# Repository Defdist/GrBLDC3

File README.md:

# GrBLDC3
Uno Shield for grblDD: closed loop spindle VFD + 4 stepper drivers

Main Controller PCB for GG3.  Hardware version 3B
This is the 1st PCB shipped in GG3.

PCB designed in KiCAD.

Changes (from the previous prototype PCB):

-3-pin header order changed from VGS to VSG (e.g. from +-X to +X-).  This creates an incompatibility issue with GG2 units, which will require a pin swap.

-Removed Door Switch (which also restored previous gap for zip tie).

-Vref changed to 1.78 volts (added 1k series with pulldown).

-Added two additional stepper power modes, to reduce power consumption at idle, and to (briefly) increase power if X axis is binding, or if BLDC controller is bogged down in a corner.

-Stepper X1 is now disabled unless A0_STEP_X1_EN is pulled high... this pin is shared with 64M1 reset, which means that when the X1 stepper (only) is disabled, the spindle will not spin.

-Replaced 2x1 screw terminal probe connector with 5x1 SIP.  This is now the only wire harness that goes to LED PCB.  24V and 5V are current limited on this PCB, so that metal chips contacting LED PCB don't affect GrBLDC.

-Added Zener protection diode to 5V rail, in the hope that if 24V finds its way onto that rail, the zener will short it out... this will of course burn out the zener, but hopefully by then the PTC on the Uno will have opened.

-Fixed incorrect pinout on A4910 (pins 39 & 40 swapped).

-BLDC Hall connector changed from 1x5 to 2x3, to make assembling easier.  6th pin is now connected to spindle wipers.

-Removed 2x3 64M1 programming header; connected SPI to Arduino pins instead.  328p can now program this part in-situ (via temporarily loading SPI bitbang firmware onto 328p).

-Emergency stop now pulls BLDC and stepper drivers into reset.

-Emergency stop interface to 328p fixed, such that computer can now pulse reset line during firmware updates.  When estop enabled, 328p continuously held in reset.

-Z stepper connector changed to 2x2, so that it fits through gantry bushings.

-24V/GND/GND 45 degree connector now fits (moved fan connector and capacitors).

New Parts:  
LED PCB:  
102-5777-ND  
Get longer right angle SIPs for LED PCB  
LED - 732-5660-1-ND

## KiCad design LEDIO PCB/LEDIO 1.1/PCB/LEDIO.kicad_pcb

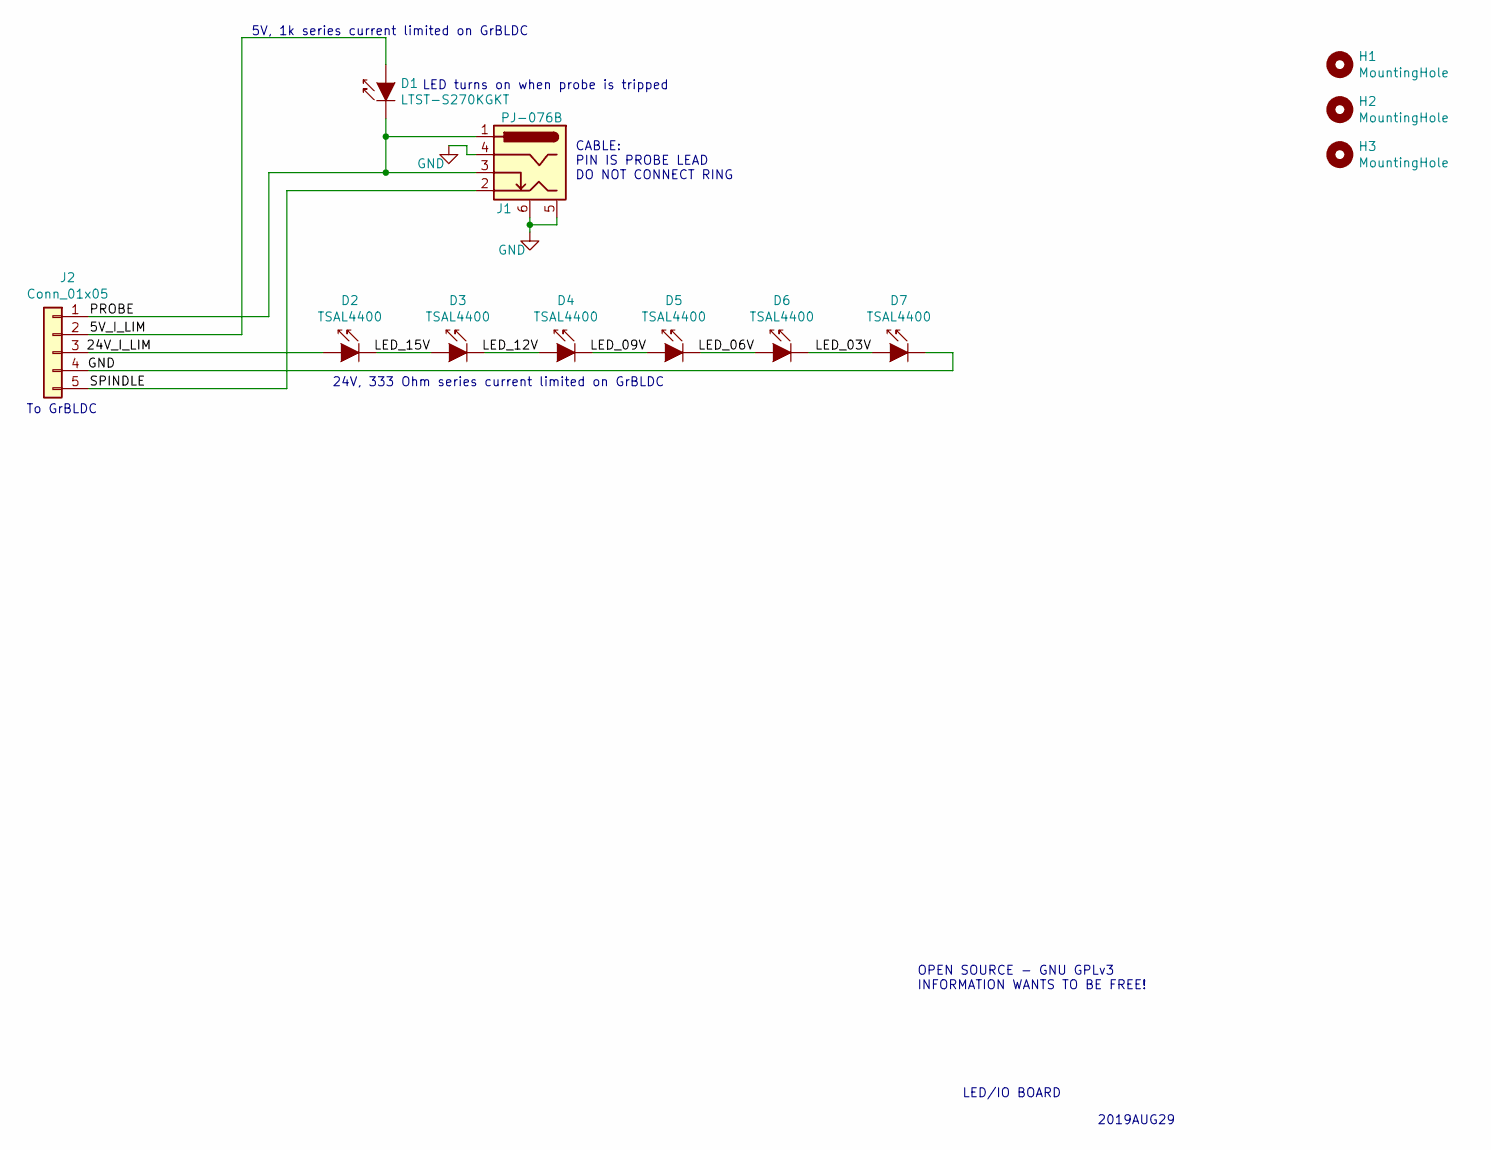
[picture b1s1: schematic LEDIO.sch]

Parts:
D1: LTST-S270KGKT; D_0603_1608Metric
D2, D3, D4, D5, D6, D7: TSAL4400; D_1206_3216Metric
H1, H2, H3: MountingHole; MountingHole_3.2mm_M3
J1: PJ-076B; CUI_PJ-076
J2: Conn_01x05; PinHeader_1x05_P2.54mm_Horizontal

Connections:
/5V_I_LIM: D1.2 (A), J2.2
/24V_I_LIM: D2.2 (A), J2.3
/LED_03V: D6.1 (K), D7.2 (A)
/LED_06V: D5.1 (K), D6.2 (A)
/LED_09V: D4.1 (K), D5.2 (A)
/LED_12V: D3.1 (K), D4.2 (A)
/LED_15V: D2.1 (K), D3.2 (A)
/PROBE: D1.1 (K), J1.1, J1.3, J2.1
/SPINDLE: J1.2, J2.5
GND: D7.1 (K), J1.4, J1.5 (ShieldA), J1.6 (ShieldB), J2.4

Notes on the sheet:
CABLE: PIN IS PROBE LEAD DO NOT CONNECT RING
2019AUG29
LED/IO BOARD
OPEN SOURCE - GNU GPLv3 INFORMATION WANTS TO BE FREE!
5V, 1k series current limited on GrBLDC
To GrBLDC
LED turns on when probe is tripped
24V, 333 Ohm series current limited on GrBLDC

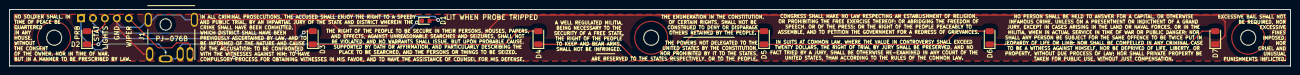
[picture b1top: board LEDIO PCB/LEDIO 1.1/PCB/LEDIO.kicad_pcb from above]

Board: 2 copper layers, 272.5 x 12.0 mm, 12 parts (1 on the bottom side), 10 nets.

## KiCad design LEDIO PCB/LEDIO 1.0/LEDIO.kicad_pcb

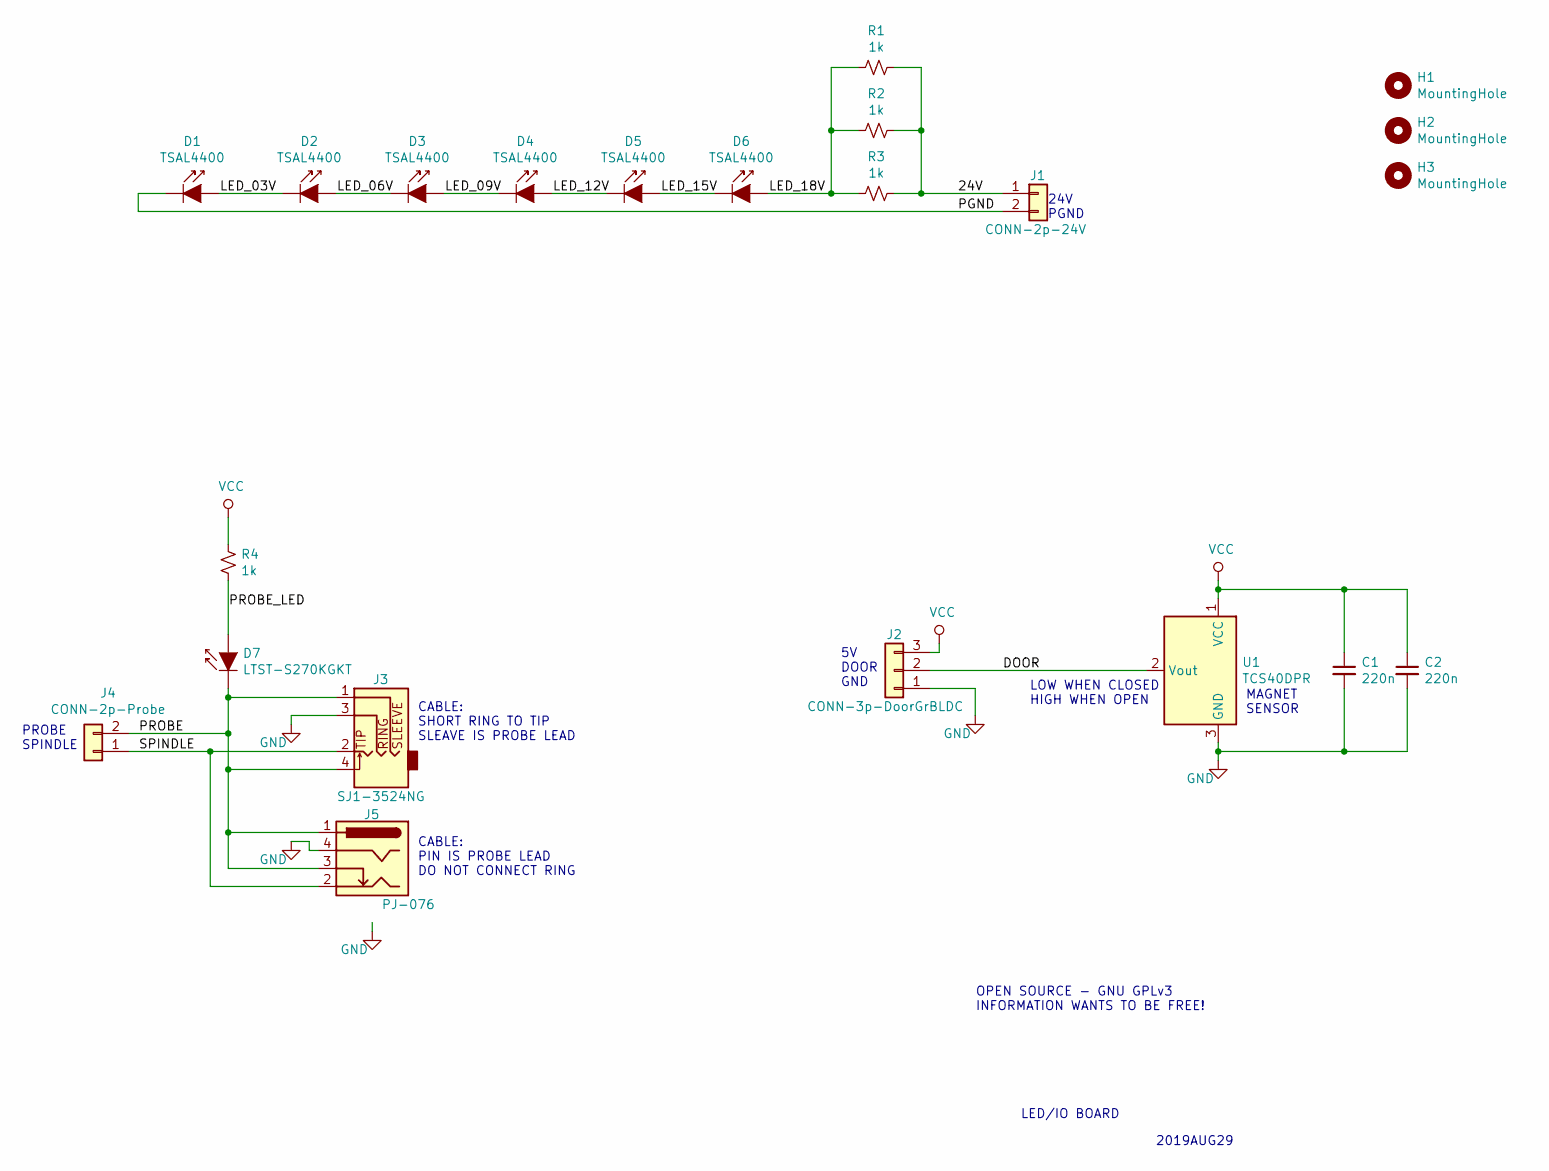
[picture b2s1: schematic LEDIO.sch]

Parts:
C1, C2: 220n; C_0603_1608Metric
D1, D2, D3, D4, D5, D6: TSAL4400; D_1206_3216Metric
D7: LTST-S270KGKT; D_0603_1608Metric
H1, H2, H3: MountingHole; MountingHole_3.2mm_M3
J1: CONN-2p-24V; PinHeader_1x02_P2.54mm_Horizontal
J2: CONN-3p-DoorGrBLDC; PinHeader_1x03_P2.54mm_Horizontal
J3: SJ1-3524NG; CUI_SJ1-3524NG
J4: CONN-2p-Probe; PinHeader_1x02_P2.54mm_Horizontal
J5: PJ-076; CUI_PJ-076
R1, R2, R3, R4: 1k; R_0603_1608Metric
U1: TCS40DPR; SOT-23

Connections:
/24V: J1.1, R1.1, R2.1, R3.1
/DOOR: J2.2, U1.2 (Vout)
/LED_03V: D1.2 (A), D2.1 (K)
/LED_06V: D2.2 (A), D3.1 (K)
/LED_09V: D3.2 (A), D4.1 (K)
/LED_12V: D4.2 (A), D5.1 (K)
/LED_15V: D5.2 (A), D6.1 (K)
/LED_18V: D6.2 (A), R1.2, R2.2, R3.2
/PGND: D1.1 (K), J1.2
/PROBE: D7.1 (K), J3.1, J3.4, J4.2, J5.1, J5.3
/PROBE_LED: D7.2 (A), R4.2
/SPINDLE: J3.2, J4.1, J5.2
GND: C1.2, C2.2, J2.1, J3.3, J5.4, U1.3 (GND)
VCC: C1.1, C2.1, J2.3, R4.1, U1.1 (VCC)

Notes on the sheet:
24V PGND
5V DOOR GND
PROBE SPINDLE
CABLE: SHORT RING TO TIP SLEAVE IS PROBE LEAD
CABLE: PIN IS PROBE LEAD DO NOT CONNECT RING
MAGNET SENSOR
2019AUG29
LED/IO BOARD
OPEN SOURCE - GNU GPLv3 INFORMATION WANTS TO BE FREE!
LOW WHEN CLOSED HIGH WHEN OPEN

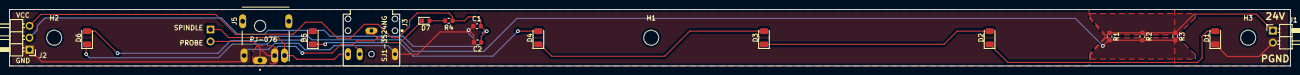
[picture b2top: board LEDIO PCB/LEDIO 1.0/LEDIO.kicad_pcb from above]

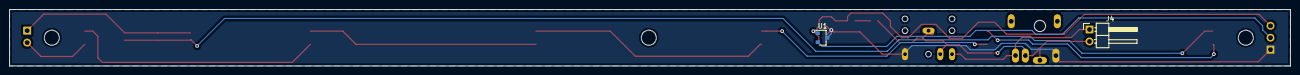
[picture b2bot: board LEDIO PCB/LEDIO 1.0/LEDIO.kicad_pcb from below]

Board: 2 copper layers, 272.5 x 12.0 mm, 22 parts (2 on the bottom side), 14 nets.

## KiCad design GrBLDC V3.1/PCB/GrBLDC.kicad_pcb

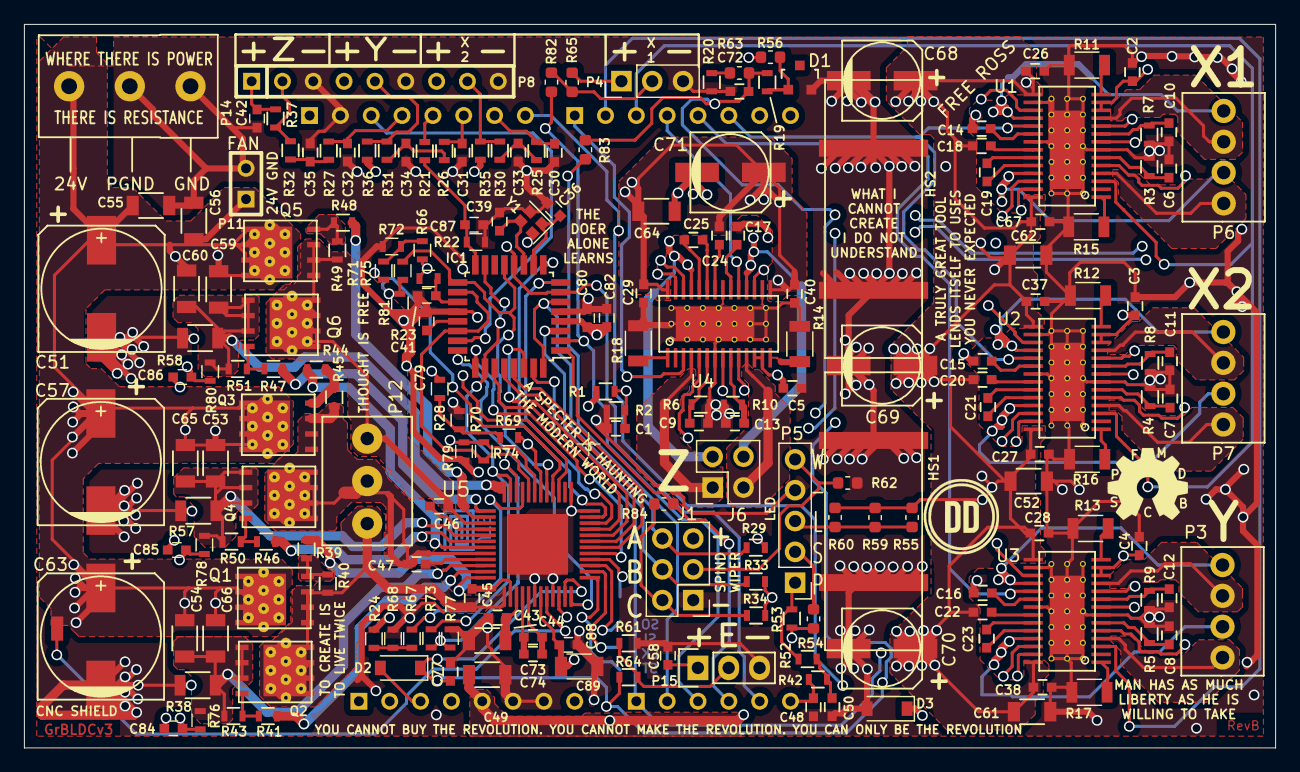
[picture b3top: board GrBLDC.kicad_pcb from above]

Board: 6 copper layers, 103.1 x 59.6 mm, 207 parts (0 on the bottom side), 145 nets.

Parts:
C1, C2, C3, C4, C5, C14, C15, C16, C17, C18, C19, C20, C21, C22, C23, C24, C25, C26, C27, C28, C29, C30, C31, C32, C33, C34, C35, C37, C38, C40, C41, C42, C43, C58, C67, C72, C73, C74, C77, C80, C82, C87, C88: 220n; C_0603
C6, C7, C8, C9, C10, C11, C12, C13, C84, C85, C86: 680p; C_0603
C36, C39: 12p; C_0603
C44, C49, C52, C53, C54, C55, C56, C59, C60, C61, C62, C64, C65, C66, C89: 10u; C_1206
C45, C46, C47, C48, C50, C79: 33n; C_0603
C51, C57, C63: 330u; c_elec_10x10.5
C68, C69, C70, C71: 100u; c_elec_493-3953-2-ND_6.3x7.7
D1: LM4040; SOT-23
D2, D3: 6V Zener; D_SOD-123
HS1, HS2: Heat_Sink; HeatSink
IC1: ATMEGA16M1-A; TQFP-32_7x7mm_Pitch0.8mm
ILTC1: 0; ILTC
J1: Conn_02x03_Odd_Even; PinHeader_2x03_P2.54mm_Vertical
J2: 4910SCK; TestPoint_Pad_D1.0mm
J3: 4910SDI; TestPoint_Pad_D1.0mm
J4: 4910SDO; TestPoint_Pad_D1.0mm
J5: 4910STR; TestPoint_Pad_1.0x1.0mm
J6: Conn_02x02_Top_Bottom; PinHeader_2x02_P2.54mm_Vertical
P1: CONN_6; ARDUINO-SIL-6
P2, P9, P10: CONN_8; ARDUINO-SIL-8
P3, P6, P7: CONN_01X04; Pin_A98335-ND_1x04
P4: CONN_01X03; PinHeader_1x03_P2.54mm_Vertical
P5: CONN_01X05; PinHeader_1x05_P2.54mm_Vertical
P8: CONN_9; SIL-9
P11: CONN_2; SIL-2
P12: CONN_01X03; 277-1722-ND
P14: CONN_01X03; Pin_Header_277-1578-ND_3x01
P15: CONN_01X03; Socket_Strip_Straight_1x03
Q1, Q2, Q3, Q4, Q5, Q6: IRF5406
R1, R2, R20, R29, R33, R34, R53, R61, R76, R77, R78, R79, R80, R81: 1.47k; R_0603
R3, R4, R5, R6, R7, R8, R9, R10, R21, R22: 56k; R_0603
R11, R12, R13, R14, R15, R16, R17, R18: 0.09; R_1206
R19, R25, R26, R27, R30, R31, R32: 1k; R_0603
R23, R39, R41, R42, R44, R46, R47, R48, R52, R64, R68, R70, R72: 47; R_0603
R24, R28, R35, R36, R37, R66: DNP; R_0603
R38, R57, R58: .005; R_1206
R40, R43, R45, R49, R50, R51: 470k; R_0603
R54, R55, R56, R59, R60, R63, R83: 1k; R_0603_1608Metric
R62, R65: DNP; R_0603_1608Metric
R67, R69, R71, R73, R74, R75: 24.3k; R_0603
R82, R84: 1.47k; R_0603_1608Metric
U1, U2, U3, U4: DRV8818
U5: A4910; A4910-LQFP_48
Y1: 16M; Crystal_SMD_2016-4pin_2.0x1.6mm

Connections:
+24V: C18.2, C20.2, C22.2, C24.2, C26.1, C27.1, C28.1, C29.1, C37.1, C38.1, C40.1, C51.1, C52.1, C53.1, C54.1, C55.1, C56.1, C57.1, C59.1, C60.1, C61.1, C62.1, C63.1, C64.1, C65.1, C66.1, C67.1, C68.1, C69.1, C70.1, C71.1, C88.1, C89.1, ILTC1.2, P11.1, P14.1, Q1.D, Q3.D, Q5.D, R55.2, R59.2, R60.2, U1.15, U1.28, U2.15, U2.28, U3.15, U3.28, U4.15, U4.28, U5.7
/2V5REF: D1.1, R19.1, R56.2
/5V_LED: P5.2, R54.2
/24V_LED: P5.3, R55.1, R59.1, R60.1
/A0_STEP_X1_EN: IC1.31, P1.1, U1.27
/A1_Stepper_PMode: P1.2, R83.1
/A2_LIMIT_X1: IC1.2, P1.3, R82.1
/A3_64M1MISO: IC1.1, P1.4, R84.1
/A4_SPINDLE_OVERLOAD: IC1.7, IC1.12, P1.5
/A5_PROBE: C48.2, P1.6, R42.1
/A4910Fault: IC1.25, U5.17
/AHI: IC1.29, U5.18
/ALO: IC1.28, U5.19
/AVCC: C41.1, IC1.19, R23.2
/BHI: IC1.30, U5.20
/BLAC_XTAL1: C36.2, IC1.10, Y1.1
/BLAC_XTAL2: C39.1, IC1.11, Y1.3
/BLAC_aRef: C79.2, IC1.21
/BLDC_En: IC1.24, U5.12
/BLO: IC1.27, U5.21
/CA: C45.1, U5.2
/CB: C47.1, U5.45
/CC: C46.1, U5.40
/CHI: IC1.8, U5.22
/CLO: IC1.9, U5.23
/CP1: C73.2, C74.2, U5.5
/CP2: C73.1, C74.1, U5.4
/CSAM: C84.2, R73.1, R77.2, U5.34
/CSAP: C84.1, R67.1, R76.2, U5.33
/CSBM: C85.2, R74.1, R79.2, U5.31
/CSBP: C85.1, R69.1, R78.2, U5.30
/CSCM: C86.2, R75.1, R81.2, U5.28
/CSCP: C86.1, R71.1, R80.2, U5.27
/CUR_A: IC1.15, IC1.26, R73.2, U5.35
/CUR_B: IC1.18, IC1.22, R74.2, U5.32
/CUR_C: IC1.13, IC1.17, R75.2, U5.29
/D2_STEP_X: P10.6, U1.19, U2.19
/D3_STEP_Y: P10.5, U3.19
/D4_STEP_Z: P10.4, U4.19
/D5_DIR_X: P10.3, U1.3, U2.3
/D6_DIR_Y: P10.2, U3.3
/D7_DIR_Z: P10.1, U4.3
/D8_STEP_EN_n: P9.8, U1.26, U2.26, U3.26, U4.26
/D9_LIMIT_X2: C30.1, P9.7, R25.2
/D10_LIMIT_Y: C31.1, P9.6, R26.2
/D11_SPIN_PWM: P9.5, R21.2
/D12_LIMIT_Z: C32.1, P9.4, R27.2
/D13_SPIN_DIR: IC1.23, P9.3
/DECAY: C1.1, R1.2, R2.1, U1.5, U2.5, U3.5, U4.5
/ESTOP_Filtered: C77.1, D2.1, R64.2, U1.17, U2.17, U3.17, U4.17, U5.11
/ESTOP_n: P15.2, R61.2, R64.1
/GHA: R39.1, U5.48
/GHAZ: Q1.G, R39.2, R40.2
/GHB: R44.1, U5.43
/GHBZ: Q3.G, R44.2, R45.2
/GHC: R48.1, U5.38
/GHCZ: Q5.G, R48.2, R49.2
/GLA: R41.1, U5.47
/GLAZ: Q2.G, R41.2, R43.1
/GLB: R46.1, U5.42
/GLBZ: Q4.G, R46.2, R50.1
/GLC: R47.1, U5.37
/GLCZ: Q6.G, R47.2, R51.1
/HALL_A: IC1.6, IC1.32, J1.6, R29.2
/HALL_B: IC1.3, J1.4, R33.2
/HALL_C: J1.2, R34.2, R84.2
/ISET_A: R24.1, R67.2, R68.2
/ISET_B: R28.1, R69.2, R70.2
/ISET_C: R66.1, R71.2, R72.2
/LSSA: C54.2, C66.2, Q2.S, R38.2, R43.2, R76.1, U5.46
/LSSB: C53.2, C65.2, Q4.S, R50.2, R57.2, R78.1, U5.41
/LSSC: C59.2, C60.2, Q6.S, R51.2, R58.2, R80.1, U5.36
/PHASE_A: C45.2, P12.1, Q1.S, Q2.D, R40.1, U5.1
/PHASE_B: C47.2, P12.2, Q3.S, Q4.D, R45.1, U5.44
/PHASE_C: C46.2, P12.3, Q5.S, Q6.D, R49.1, U5.39
/PI_PRB: C50.2, R42.2, R52.1
/PI_X2LIM: C33.1, R25.1, R30.2
/PI_YLIM: C34.1, R26.1, R31.2
/PI_ZLIM: C35.1, R27.1, R32.2
/PROBE_NOISY: P5.1, R52.2, R53.2
/RESET_328p: D2.2, P2.3
/SPIN_PWM_to_Analog: C87.2, IC1.16, R21.1, R22.1
/Spindle_Wiper: J1.3, P5.5, R62.2
/VBRG: ILTC1.1, U5.8
/VREF_DIV: R20.1, R63.2
/VREF_Steppers: C72.1, R19.2, R63.1, R83.2, U1.8, U2.8, U3.8, U4.8
/VREG: C43.1, C44.1, U5.3
/X1LIM: P4.2, R65.1, R82.2
/X1_A1: P6.1, U1.4
/X1_A2: P6.2, U1.25
/X1_B1: P6.3, U1.11
/X1_B2: P6.4, U1.18
/X1_CP1: C19.1, U1.23
/X1_CP2: C19.2, U1.24
/X1_ISENA: R15.1, U1.1
/X1_ISENB: R11.1, U1.14
/X1_RCA: C6.1, R3.1, U1.6
/X1_RCB: C10.1, R7.1, U1.9
/X1_VCP: C18.1, U1.22
/X1_VGD: C14.1, U1.20
/X2LIM: P8.8, R30.1, R35.1
/X2_A1: P7.1, U2.4
/X2_A2: P7.2, U2.25
/X2_B1: P7.3, U2.11
/X2_B2: P7.4, U2.18
/X2_CP1: C21.1, U2.23
/X2_CP2: C21.2, U2.24
/X2_ISENA: R16.1, U2.1
/X2_ISENB: R12.1, U2.14
/X2_RCA: C7.1, R4.1, U2.6
/X2_RCB: C11.1, R8.1, U2.9
/X2_VCP: C20.1, U2.22
/X2_VGD: C15.1, U2.20
/YLIM: P8.5, R31.1, R36.1
/Y_A1: P3.1, U3.4
/Y_A2: P3.2, U3.25
/Y_B1: P3.3, U3.11
/Y_B2: P3.4, U3.18
/Y_CP1: C23.1, U3.23
/Y_CP2: C23.2, U3.24
/Y_ISENA: R17.1, U3.1
/Y_ISENB: R13.1, U3.14
/Y_RCA: C8.1, R5.1, U3.6
/Y_RCB: C12.1, R9.1, U3.9
/Y_VCP: C22.1, U3.22
/Y_VGD: C16.1, U3.20
/ZLIM: P8.2, R32.1, R37.1
/Z_A1: J6.1, U4.4
/Z_A2: J6.2, U4.25
/Z_B1: J6.3, U4.11
/Z_B2: J6.4, U4.18
/Z_CP1: C25.1, U4.23
/Z_CP2: C25.2, U4.24
/Z_ISENA: R18.1, U4.1
/Z_ISENB: R14.1, U4.14
/Z_RCA: C9.1, R6.1, U4.6
/Z_RCB: C13.1, R10.1, U4.9
/Z_VCP: C24.1, U4.22
/Z_VGD: C17.1, U4.20
/a4910_SCK: J2.1, U5.14
/a4910_SDI: J3.1, U5.15
/a4910_SDO: J4.1, U5.16
/a4910_STRn: J5.1, U5.13
GND: C1.2, C2.2, C3.2, C4.2, C5.2, C6.2, C7.2, C8.2, C9.2, C10.2, C11.2, C12.2, C13.2, C14.2, C15.2, C16.2, C17.2, C26.2, C27.2, C28.2, C29.2, C30.2, C31.2, C32.2, C33.2, C34.2, C35.2, C36.1, C37.2, C38.2, C39.2, C40.2, C41.2, C42.2, C43.2, C44.2, C48.1, C49.2, C50.1, C51.2, C52.2, C55.2, C56.2, C57.2, C58.2, C61.2, C62.2, C63.2, C64.2, C67.2, C68.2, C69.2, C70.2, C71.2, C72.2, C77.2, C79.1, C80.2, C82.2, C87.1, C88.2, C89.2, D1.2, D3.2, HS1.1, HS1.2, HS2.1, HS2.2, IC1.5, IC1.20, J1.1, P2.6, P2.7, P4.3, P5.4, P8.3, P8.6, P8.9, P9.2, P11.2, P14.2, P14.3, P15.3, R2.2, R3.2, R4.2, R5.2, R6.2, R7.2, R8.2, R9.2, R10.2, R11.2, R12.2, R13.2, R14.2, R15.2, R16.2, R17.2, R18.2, R20.2, R22.2, R38.1, R57.1, R58.1, R61.1, R62.1, R68.1, R70.1, R72.1, R77.1, R79.1, R81.1, U1.7, U1.16, U1.21, U1.29, U2.7, U2.16, U2.21, U2.29, U3.7, U3.16, U3.21, U3.29, U4.7, U4.16, U4.21, U4.29, U5.6, U5.9, U5.24, U5.25, U5.49, Y1.2, Y1.4
VCC: C2.1, C3.1, C4.1, C5.1, C42.1, C49.1, C58.1, C80.1, C82.1, D3.1, IC1.4, J1.5, P2.5, P4.1, P8.1, P8.4, P8.7, P15.1, R1.1, R23.1, R24.2, R28.2, R29.1, R33.1, R34.1, R35.2, R36.2, R37.2, R53.1, R54.1, R56.1, R65.2, R66.2, U1.10, U1.12, U1.13, U2.10, U2.12, U2.13, U2.27, U3.10, U3.12, U3.13, U3.27, U4.10, U4.12, U4.13, U4.27, U5.10

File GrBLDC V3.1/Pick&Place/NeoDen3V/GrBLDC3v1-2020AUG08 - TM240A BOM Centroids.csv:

Stack,Nozzle,Name,Value,Footprint,X,Y,Rotation,Skip
4,2,R55,1K0R,603,18.95,29.7,90,0
4,2,R59,1K0R,603,18.95,32.75,90,0
4,2,R60,1K0R,603,18.95,36.04,90,0
4,2,R54,1K0R,603,10.65,37.87,90,0
4,2,R56,1K0R,603,56.78,41.32,0,0
4,2,R19,1K0R,603,54.86,41.64,90,0
4,2,R63,1K0R,603,55.4,43.82,0,0
4,2,R83,1K0R,603,49.3,56.62,90,0
4,2,R25,1K0R,603,49.2,60.65,90,0
4,2,R30,1K0R,603,49.23,63.67,90,0
8,2,R70,47R,603,26.97,66.97,90,0
4,2,R26,1K0R,603,49.2,68.24,90,0
8,2,R68,47R,603,9.02,72.46,90,0
8,2,R72,47R,603,41.32,72.44,0,0
4,2,R31,1K0R,603,49.2,72.96,90,0
4,2,R27,1K0R,603,49.18,77.73,90,0
4,2,R32,1K0R,603,49.25,80.8,90,0
8,2,R42,47R,603,5.57,37.59,0,0
8,2,R52,47R,603,7.23,38.43,0,0
8,2,R64,47R,603,5.8,53.22,0,0
8,2,R23,47R,603,38.62,69.58,0,0
8,2,R48,47R,603,43.24,76.48,0,0
8,2,R44,47R,603,31.06,78.86,0,0
8,2,R39,47R,603,16.21,79.4,90,0
8,2,R47,47R,603,31.18,82.41,0,0
8,2,R41,47R,603,2.61,82.93,0,0
8,2,R46,47R,603,16.99,83.02,0,0
9,2,C50,33nF,603,3.43,36.33,90,0
9,2,C48,33nF,603,3.42,37.88,90,0
9,2,C45,33nF,603,12.37,66.01,90,0
9,2,C46,33nF,603,19.93,68.72,0,0
9,2,C79,33nF,603,35.21,69.75,90,0
9,2,C47,33nF,603,15.15,70.58,0,0
1,2,R8,56K0R,603,31.62,10.02,90,0
1,2,R4,56K0R,603,28.9,10.1,90,0
1,2,R5,56K0R,603,9.3,10.14,90,0
1,2,R9,56K0R,603,12.16,10.14,90,0
1,2,R3,56K0R,603,47.75,10.1,90,0
1,2,R7,56K0R,603,50.45,10.1,90,0
1,2,R10,56K0R,603,28.13,44.36,0,0
1,2,R6,56K0R,603,28.15,47.07,0,0
1,2,R22,56K0R,603,41.6,65.69,0,0
1,2,R28,DNP,603,29.65,68.66,90,1
1,2,R21,56K0R,603,49.14,69.81,90,0
1,2,R66,DNP,603,40.99,70.03,90,1
1,2,R24,56K0R,603,9.1,74.03,90,1
14,2,C36,12pF,603,44.39,59.38,-45,0
14,2,C39,12pF,603,43.38,63.49,90,0
3,2,C7,680pF,603,28.7,8.24,90,0
3,2,C11,680pF,603,31.73,8.27,90,0
3,2,C12,680pF,603,12.27,8.41,90,0
3,2,C8,680pF,603,9.19,8.41,90,0
3,2,C10,680pF,603,50.6,8.37,90,0
3,2,C6,680pF,603,47.6,8.37,90,0
3,2,C13,680pF,603,26.67,44.25,0,0
3,2,C9,680pF,603,26.67,47.22,0,0
3,2,C86,680pF,603,30.52,89.78,0,0
3,2,C85,680pF,603,16.27,90.23,0,0
3,2,C84,680pF,603,1.58,90.51,0,0
6,2,R53,1K47R,603,10.58,39.45,90,0
6,2,R62,DNP,603,21.74,34.86,0,1
6,2,R34,1K47R,603,10.83,42.46,0,0
6,2,R33,1K47R,603,13.63,42.47,0,0
6,2,R29,1K47R,603,16.42,42.48,0,0
6,2,R20,1K47R,603,54.73,46.04,90,0
6,2,R84,1K47R,603,20.01,50.05,0,0
6,2,R61,1K47R,603,8.54,52.97,0,0
6,2,R2,1K47R,603,27.75,53.99,0,0
6,2,R1,1K47R,603,29.29,54.86,0,0
6,2,R65,DNP,603,54.76,57.61,90,1
6,2,R82,1K47R,603,54.81,59.32,90,0
6,2,R35,DNP,603,49.13,65.17,90,1
6,2,R79,1K47R,603,24.34,66.51,90,0
6,2,R77,1K47R,603,8.98,67.67,90,0
6,2,R81,1K47R,603,36.58,71.8,90,0
6,2,R36,DNP,603,49.13,74.49,90,1
6,2,R37,DNP,603,51.78,82.05,90,1
6,2,R80,1K47R,603,30.92,87.43,90,0
6,2,R78,1K47R,603,16.64,87.91,90,0
6,2,R76,1K47R,603,2.2,88.25,90,0
5,2,C4,220nF,603,16.56,10.83,90,0
5,2,C3,220nF,603,36.31,11.17,90,0
5,2,C2,220nF,603,55.6,11.4,90,0
5,2,C38,220nF,603,4.92,18.9,0,0
5,2,C67,220nF,603,43.24,18.98,0,0
5,2,C27,220nF,603,24.12,19.03,0,0
5,2,C28,220nF,603,17.61,19.06,0,0
5,2,C37,220nF,603,36.7,19.37,0,0
5,2,C26,220nF,603,55.68,19.4,0,0
5,2,C21,220nF,603,28,23.3,90,0
5,2,C19,220nF,603,47.33,23.38,90,0
5,2,C23,220nF,603,8.92,23.41,90,0
5,2,C16,220nF,603,12.69,23.73,0,0
5,2,C15,220nF,603,31.78,23.74,0,0
5,2,C22,220nF,603,11.1,23.74,0,0
5,2,C20,220nF,603,30.26,23.75,0,0
5,2,C18,220nF,603,49.52,23.81,0,0
5,2,C14,220nF,603,50.94,23.82,0,0
5,2,C40,220nF,603,37.33,39.23,90,0
5,2,C5,220nF,603,29.55,39.41,0,0
5,2,C72,220nF,603,54,43.77,0,0
5,2,C17,220nF,603,42.13,43.98,90,0
5,2,C24,220nF,603,42.13,45.43,90,0
5,2,C25,220nF,603,41.77,47.56,0,0
5,2,C58,220nF,603,7.51,49.67,90,0
5,2,C29,220nF,603,37.37,51.67,90,0
5,2,C1,220nF,603,26.24,53.95,0,0
5,2,C82,220nF,603,35.34,54.71,90,0
5,2,C80,220nF,603,35.33,56.33,90,0
5,2,C88,220nF,603,8.41,57.87,0,0
5,2,C30,220nF,603,48.95,59.01,90,0
5,2,C73,220nF,603,9.04,60.79,0,0
5,2,C74,220nF,603,7.65,60.79,0,0
5,2,C33,220nF,603,48.97,62.01,90,0
5,2,C43,220nF,603,10.65,63.73,0,0
5,2,C87,220nF,603,43.02,65.64,0,0
5,2,C31,220nF,603,48.96,66.62,90,0
5,2,C77,220nF,603,6.19,67.58,90,0
5,2,C41,220nF,603,37.16,69.53,0,0
5,2,C34,220nF,603,48.97,71.25,90,0
5,2,C32,220nF,603,48.97,76.07,90,0
5,2,C35,220nF,603,48.97,79.14,90,0
5,2,C42,220nF,603,51.77,83.52,90,0
10,2,R49,470K0R,603,40.86,76.86,90,0
10,2,R45,470K0R,603,28.76,77.11,90,0
10,2,R40,470K0R,603,13.44,77.64,90,0
10,2,R51,470K0R,603,31.14,85.21,0,0
10,2,R43,470K0R,603,2.54,85.57,0,0
10,2,R50,470K0R,603,16.92,85.72,0,0
11,2,R69,24K3R,603,25.5,62.86,0,0
11,2,R74,24K3R,603,24.35,64.84,90,0
11,2,R73,24K3R,603,8.98,69.23,90,0
11,2,R67,24K3R,603,8.92,70.86,90,0
11,2,R75,24K3R,603,39.23,71.62,90,0
11,2,R71,24K3R,603,39.24,73.19,90,0
7,2,C61,10uF,1206,2.8,19.85,0,0
7,2,C52,10uF,1206,21.8,20.14,0,0
7,2,C62,10uF,1206,40.4,20.18,0,0
7,2,C64,10uF,1206,44.1,50.81,0,0
7,2,C89,10uF,1206,6.7,57.23,0,0
7,2,C49,10uF,1206,6.05,64.76,0,0
7,2,C44,10uF,1206,8.85,64.76,0,0
7,2,C59,10uF,1206,37.8,86.89,90,0
7,2,C53,10uF,1206,23.47,87.14,90,0
7,2,C66,10uF,1206,9.04,87.14,90,0
7,2,C56,10uF,1206,43.43,88.93,90,0
7,2,C60,10uF,1206,37.84,89.53,90,0
7,2,C65,10uF,1206,23.47,89.63,90,0
7,2,C54,10uF,1206,9.04,89.68,90,0
7,2,C55,10uF,1206,44.7,92.46,0,0
12,2,R58,0R005,1206,33.78,88.51,0,0
12,2,R57,0R005,1206,19.56,88.66,0,0
12,2,R38,0R005,1206,5.18,88.71,0,0
2,2,R13,0R090,1206,18.1,14.95,0,0
2,2,R17,0R090,1206,4.69,14.95,0,0
2,2,R12,0R090,1206,37.27,15.05,0,0
2,2,R16,0R090,1206,23.85,15.05,0,0
2,2,R11,0R090,1206,56.2,15.1,0,0
2,2,R15,0R090,1206,43,15.1,0,0
2,2,R14,0R090,1206,33.3,39.09,90,0
2,2,R18,0R090,1206,33.34,52.4,90,0
13,2,D3,Zener6V,SOD123,3.25,31.86,135,0
13,2,D2,Zener6V,SOD123,6.6,71.91,135,0
,,,,,,,,
,,,,,,,,
,,,,,,,,
,,,,,,,,
,,,,,,,,
Reel,Nozzle,Reference,Comment,,X(mm),Y(mm),Rotation,SKip
16,2,Y1,OSC16MHZ,SMD2016,43.45,61.08,-45,0
15,2,D1,LM4040,SOT23,55.35,38.79,-90,0
25,1,Q1,IRF5406,PQFN8(5x6),12.38,82.08,90,0
25,1,Q2,IRF5406,PQFN8(5x6),6.3,82.3,-90,0
25,1,Q3,IRF5406,PQFN8(5x6),26.67,81.95,90,0
25,1,Q4,IRF5406,PQFN8(5x6),20.7,82.14,-90,0
25,1,Q5,IRF5406,PQFN8(5x6),40.78,81.5,90,0
25,1,Q6,IRF5406,PQFN8(5x6),34.91,81.55,-90,0
27,1,U1,DRV8818,TSSOP28,49.3,16.7,90,0
27,1,U2,DRV8818,TSSOP28,30.36,16.87,90,0
27,1,U3,DRV8818,TSSOP28,11.04,16.77,90,0
27,1,U4,DRV8818,TSSOP28,34.86,45.69,0,0
26,1,IC1,ATmega32M1,TQFP32(7x7),36.25,62.76,90,0
0,1,U5,A4910,LQFP48,16.99,60.7,0,0

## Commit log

2020-01-06 Initial Upload
    PCB is complete. This is the shipping version.
2020-01-23 Changed opamp gain offset
    opamp offset functionality (i.e. 0A = 8- mV) made gain non-uniform. Removed opamp offset entirely, as we don't really need it, and I'd rather integrate current more linearly.
2021-12-14 Added latest version and cleaned up
2021-12-14 Deleted Large Files
2021-12-14 Added readme
